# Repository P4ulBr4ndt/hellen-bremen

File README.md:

# Hellen-Bremen

**WIP. Untested.**

This is trying to be yet another HD ECU based on rusEFI.\
Commercial rusEFI based HD ECUs:\
https://www.nmstec.ca/product/hdrevb/ This seems to be the initial community development? 
https://impactwiringsolutions.com/ Commercial product

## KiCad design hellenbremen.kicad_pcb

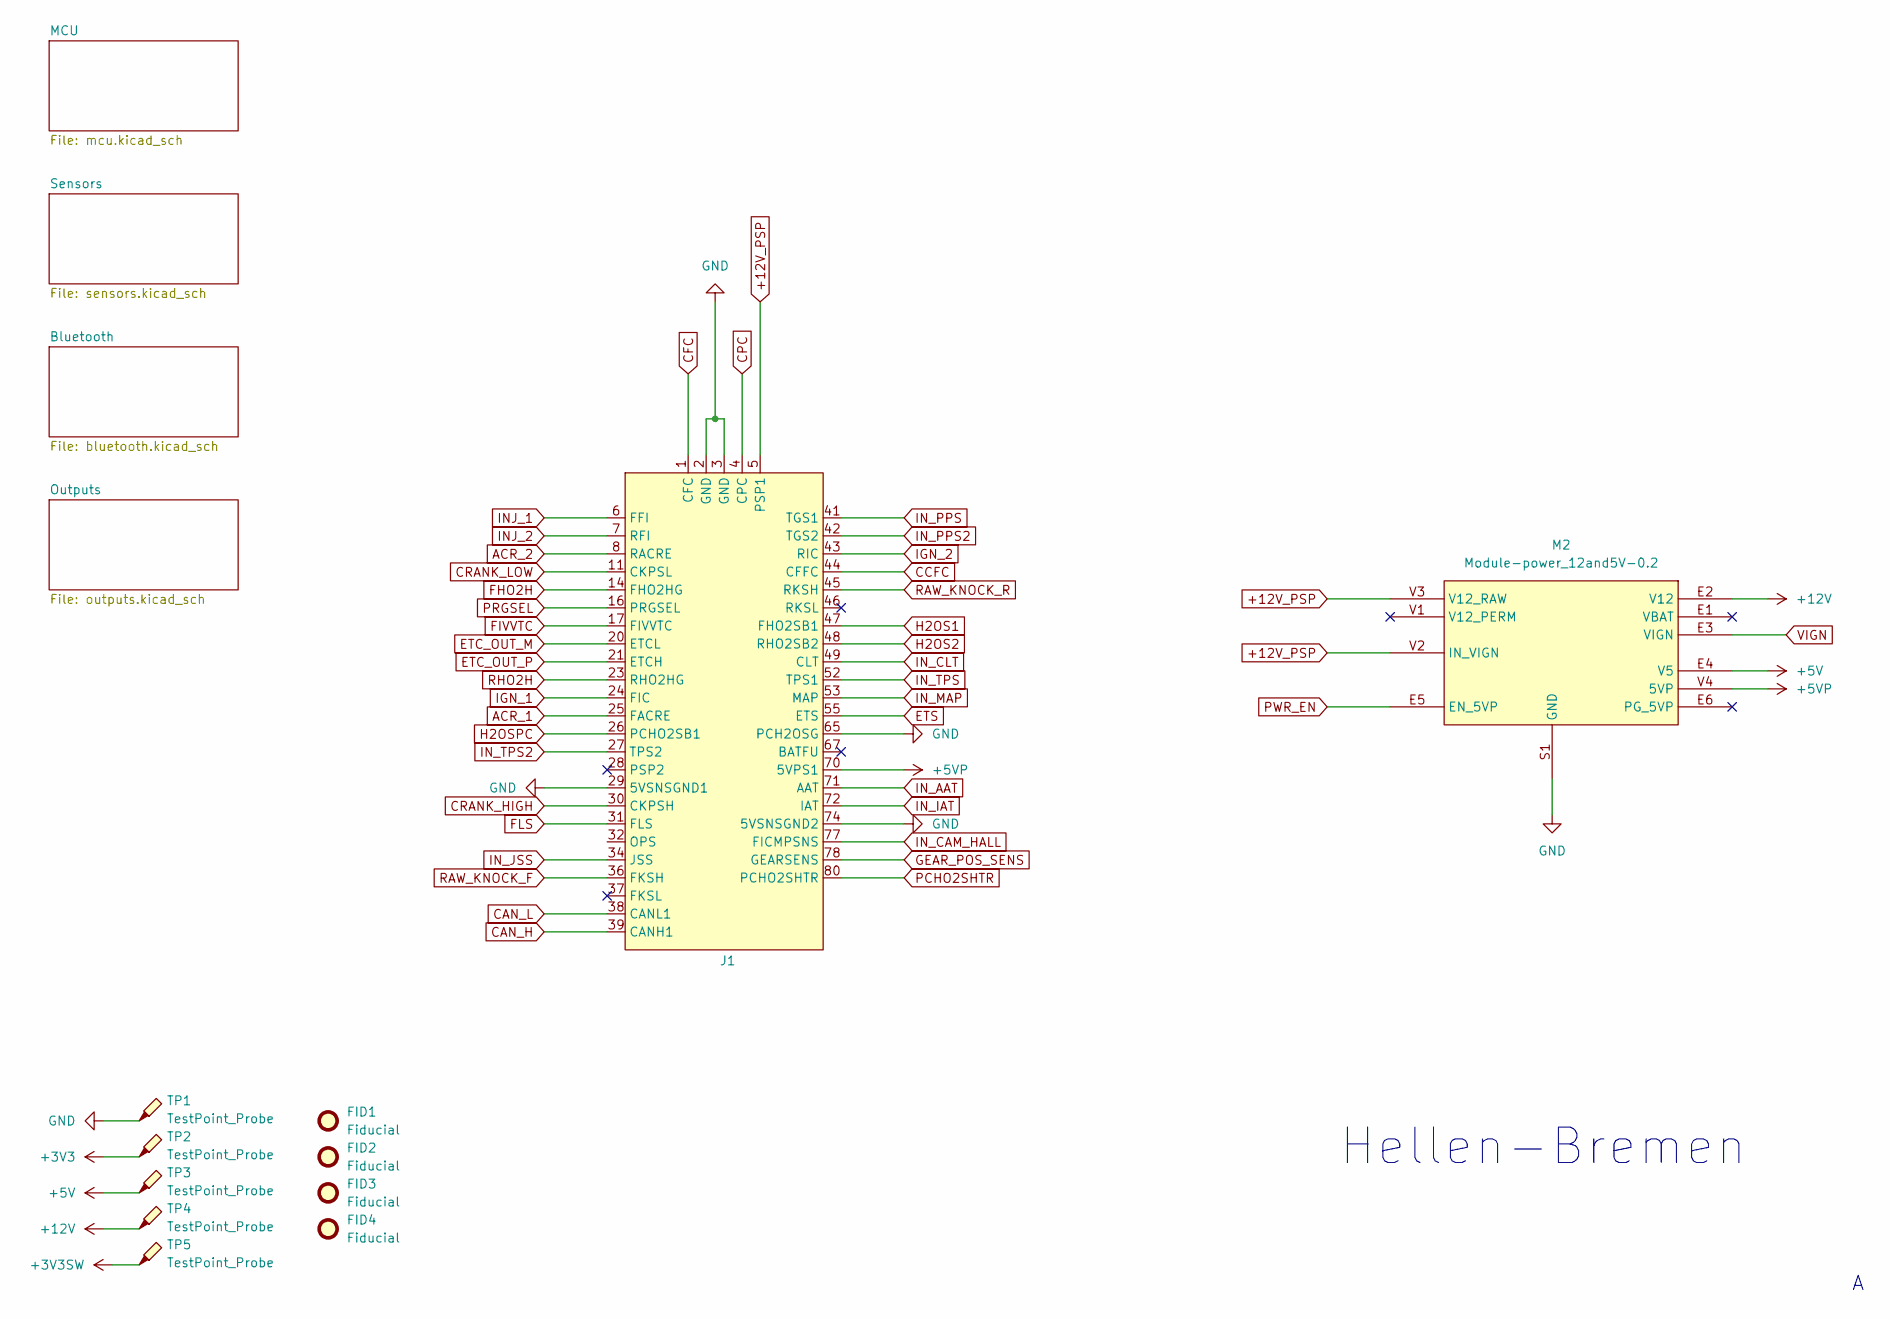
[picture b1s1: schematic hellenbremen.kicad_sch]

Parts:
FID1, FID2, FID3, FID4: Fiducial; Fiducial_1mm_Mask2mm
J1: HarleyDavidsonDelphi81
M2: Module-power_12and5V-0.2; power_12and5V
TP1, TP2, TP3, TP4, TP5: TestPoint_Probe; TestPoint_Pad_D2.0mm

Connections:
+3V3: TP2.1; also elsewhere on the board
+3V3SW: TP5.1; also elsewhere on the board
+5V: M2.E4 (V5), TP3.1; also elsewhere on the board
+5VP: J1.70 (5VPS1), M2.V4 (5VP)
+12V: M2.E2 (V12), TP4.1; also elsewhere on the board
+12V_PSP: J1.5 (PSP1), M2.V2 (IN_VIGN), M2.V3 (V12_RAW)
ACR_1: J1.25 (FACRE); also elsewhere on the board
ACR_2: J1.8 (RACRE); also elsewhere on the board
CAN_H: J1.39 (CANH1); also elsewhere on the board
CAN_L: J1.38 (CANL1); also elsewhere on the board
CCFC: J1.44 (CFFC); also elsewhere on the board
CFC: J1.1 (CFC); also elsewhere on the board
CPC: J1.4 (CPC); also elsewhere on the board
CRANK_HIGH: J1.30 (CKPSH); also elsewhere on the board
CRANK_LOW: J1.11 (CKPSL); also elsewhere on the board
ETC_OUT_M: J1.20 (ETCL); also elsewhere on the board
ETC_OUT_P: J1.21 (ETCH); also elsewhere on the board
ETS: J1.55 (ETS); also elsewhere on the board
FHO2H: J1.14 (FHO2HG); also elsewhere on the board
FIVVTC: J1.17 (FIVVTC); also elsewhere on the board
FLS: J1.31 (FLS); also elsewhere on the board
GEAR_POS_SENS: J1.78 (GEARSENS); also elsewhere on the board
GND: J1.2 (GND), J1.3 (GND), J1.29 (5VSNSGND1), J1.65 (PCH2OSG), J1.74 (5VSNSGND2), M2.S1 (GND), TP1.1; also elsewhere on the board
H2OS1: J1.47 (FHO2SB1); also elsewhere on the board
H2OS2: J1.48 (RHO2SB2); also elsewhere on the board
H2OSPC: J1.26 (PCHO2SB1); also elsewhere on the board
IGN_1: J1.24 (FIC); also elsewhere on the board
IGN_2: J1.43 (RIC); also elsewhere on the board
INJ_1: J1.6 (FFI); also elsewhere on the board
INJ_2: J1.7 (RFI); also elsewhere on the board
IN_AAT: J1.71 (AAT); also elsewhere on the board
IN_CAM_HALL: J1.77 (FICMPSNS); also elsewhere on the board
IN_CLT: J1.49 (CLT); also elsewhere on the board
IN_IAT: J1.72 (IAT); also elsewhere on the board
IN_JSS: J1.34 (JSS); also elsewhere on the board
IN_MAP: J1.53 (MAP); also elsewhere on the board
IN_PPS: J1.41 (TGS1); also elsewhere on the board
IN_PPS2: J1.42 (TGS2); also elsewhere on the board
IN_TPS: J1.52 (TPS1); also elsewhere on the board
IN_TPS2: J1.27 (TPS2); also elsewhere on the board
PCHO2SHTR: J1.80 (PCHO2SHTR); also elsewhere on the board
PRGSEL: J1.16 (PRGSEL); also elsewhere on the board
PWR_EN: M2.E5 (EN_5VP); also elsewhere on the board
RAW_KNOCK_F: J1.36 (FKSH); also elsewhere on the board
RAW_KNOCK_R: J1.45 (RKSH); also elsewhere on the board
RHO2H: J1.23 (RHO2HG); also elsewhere on the board
VIGN: M2.E3 (VIGN); also elsewhere on the board

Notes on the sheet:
Hellen-Bremen

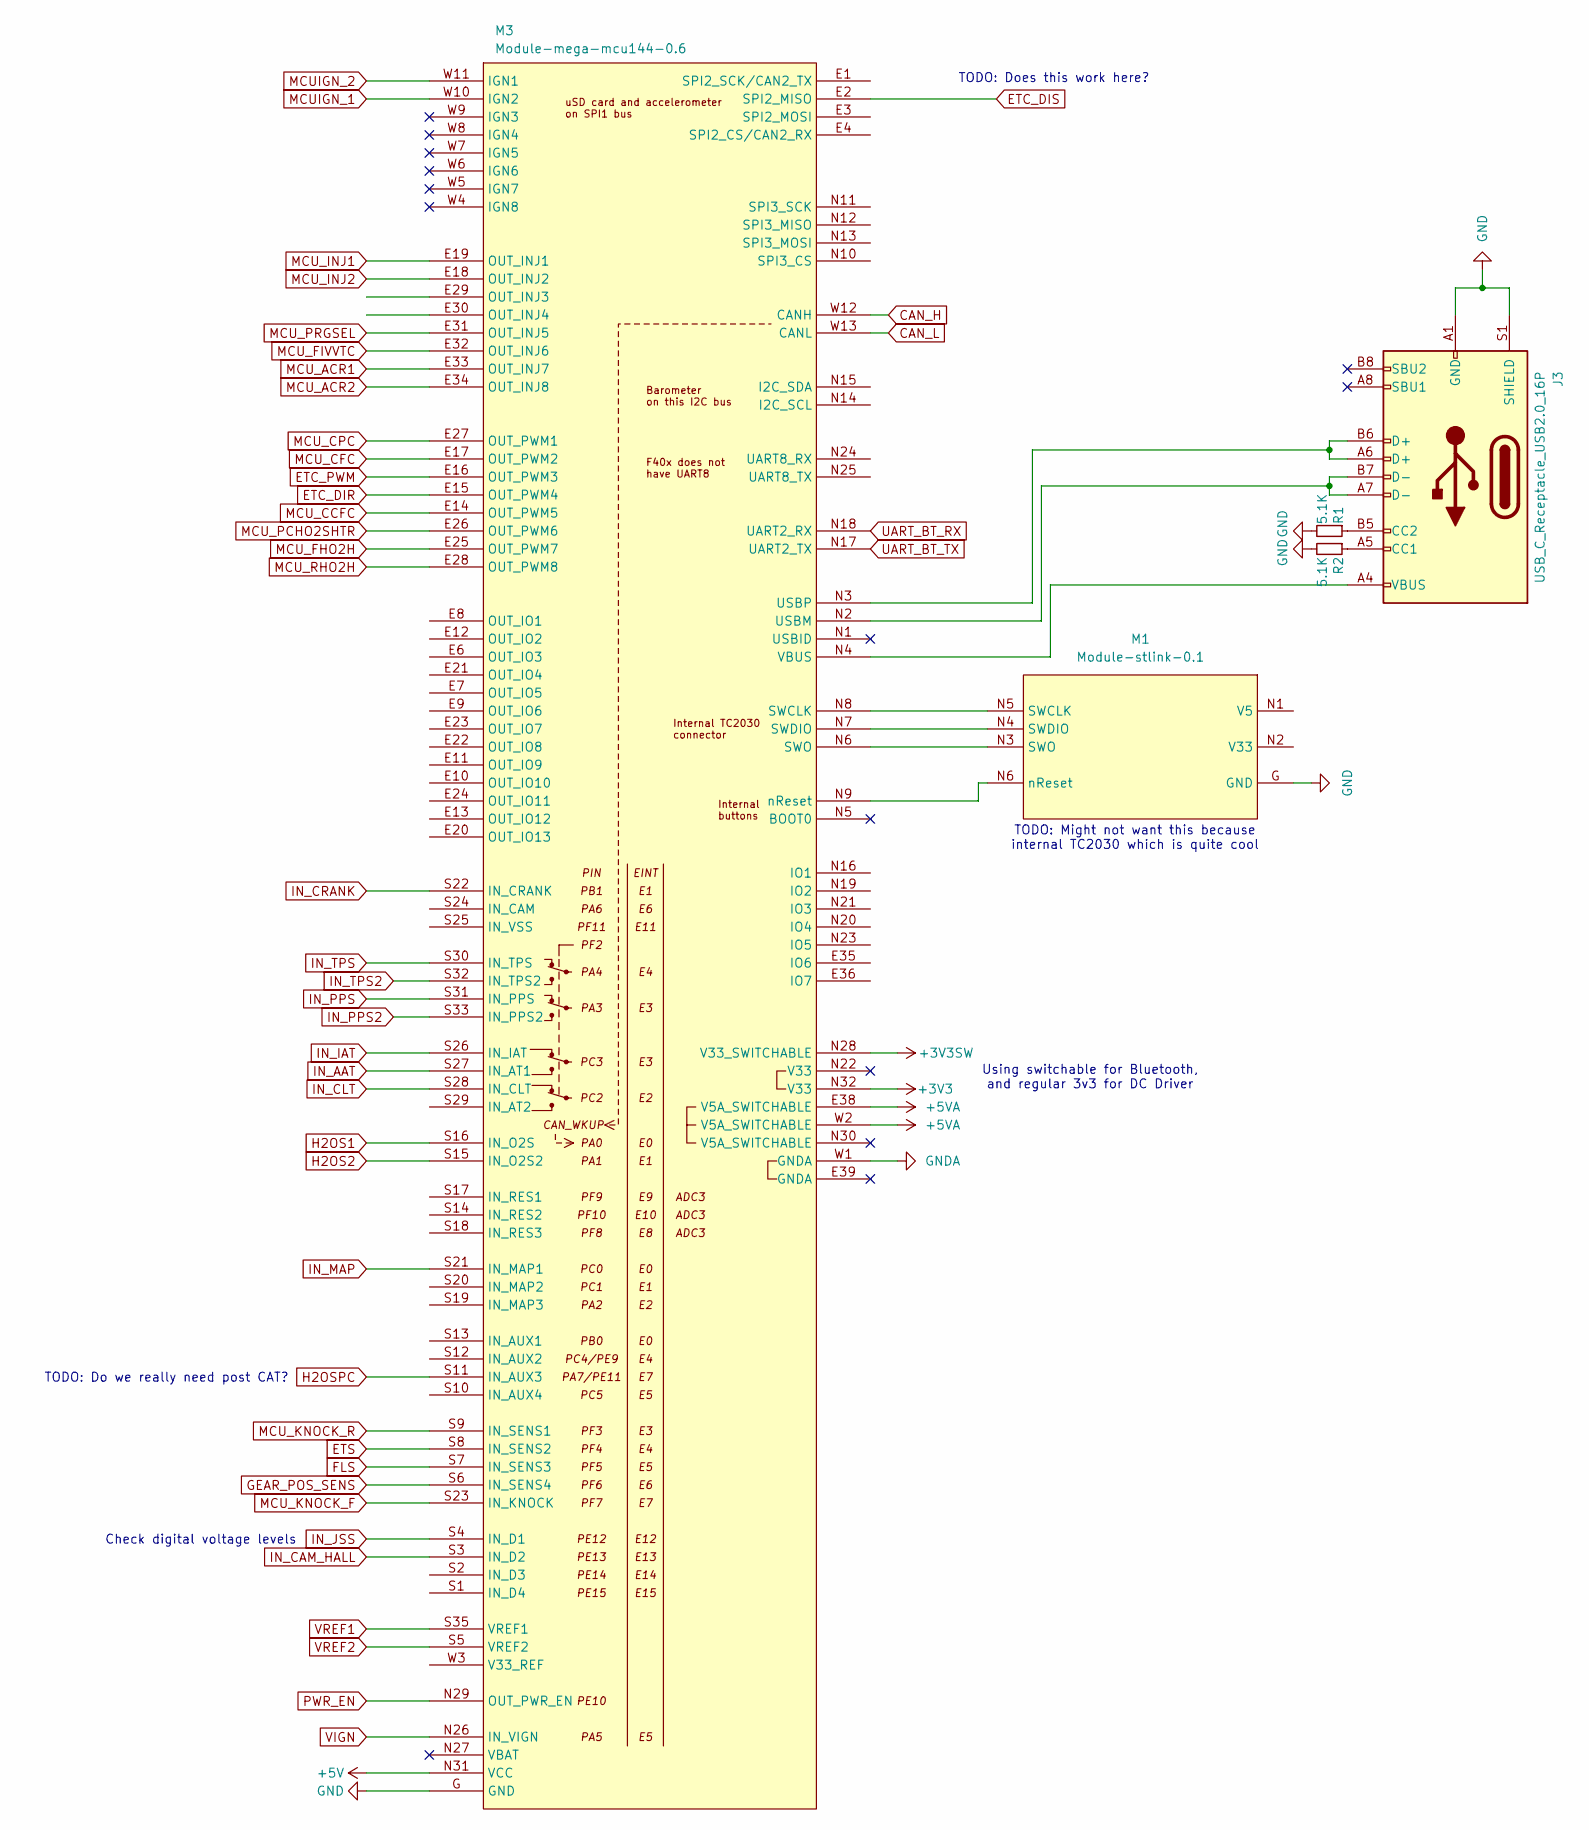
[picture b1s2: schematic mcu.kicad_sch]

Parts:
J3: USB_C_Receptacle_USB2.0_16P; USB_C_Receptacle_GCT_USB4110
M1: Module-stlink-0.1; stlink
M3: Module-mega-mcu144-0.6; mega-mcu144
R1, R2: 5.1K; R_0402_1005Metric

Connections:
+3V3: M3.N32 (V33); also elsewhere on the board
+3V3SW: M3.N28 (V33_SWITCHABLE); also elsewhere on the board
+5V: M3.N31 (VCC); also elsewhere on the board
+5VA: M3.E38 (V5A_SWITCHABLE), M3.W2 (V5A_SWITCHABLE); also elsewhere on the board
CAN_H: M3.W12 (CANH); also elsewhere on the board
CAN_L: M3.W13 (CANL); also elsewhere on the board
ETC_DIR: M3.E15 (OUT_PWM4); also elsewhere on the board
ETC_DIS: M3.E2 (SPI2_MISO); also elsewhere on the board
ETC_PWM: M3.E16 (OUT_PWM3); also elsewhere on the board
ETS: M3.S8 (IN_SENS2); also elsewhere on the board
FLS: M3.S7 (IN_SENS3); also elsewhere on the board
GEAR_POS_SENS: M3.S6 (IN_SENS4); also elsewhere on the board
GND: J3.A1 (GND), J3.A12 (GND), J3.B1 (GND), J3.B12 (GND), J3.S1 (SHIELD), M1.G (GND), M3.G (GND), R1.2, R2.2; also elsewhere on the board
GNDA: M3.W1 (GNDA)
H2OS1: M3.S16 (IN_O2S); also elsewhere on the board
H2OS2: M3.S15 (IN_O2S2); also elsewhere on the board
H2OSPC: M3.S11 (IN_AUX3); also elsewhere on the board
IN_AAT: M3.S27 (IN_AT1); also elsewhere on the board
IN_CAM_HALL: M3.S3 (IN_D2); also elsewhere on the board
IN_CLT: M3.S28 (IN_CLT); also elsewhere on the board
IN_CRANK: M3.S22 (IN_CRANK); also elsewhere on the board
IN_IAT: M3.S26 (IN_IAT); also elsewhere on the board
IN_JSS: M3.S4 (IN_D1); also elsewhere on the board
IN_MAP: M3.S21 (IN_MAP1); also elsewhere on the board
IN_PPS: M3.S31 (IN_PPS); also elsewhere on the board
IN_PPS2: M3.S33 (IN_PPS2); also elsewhere on the board
IN_TPS: M3.S30 (IN_TPS); also elsewhere on the board
IN_TPS2: M3.S32 (IN_TPS2); also elsewhere on the board
MCUIGN_1: M3.W10 (IGN2); also elsewhere on the board
MCUIGN_2: M3.W11 (IGN1); also elsewhere on the board
MCU_ACR1: M3.E33 (OUT_INJ7); also elsewhere on the board
MCU_ACR2: M3.E34 (OUT_INJ8); also elsewhere on the board
MCU_CCFC: M3.E14 (OUT_PWM5); also elsewhere on the board
MCU_CFC: M3.E17 (OUT_PWM2); also elsewhere on the board
MCU_CPC: M3.E27 (OUT_PWM1); also elsewhere on the board
MCU_FHO2H: M3.E25 (OUT_PWM7); also elsewhere on the board
MCU_FIVVTC: M3.E32 (OUT_INJ6); also elsewhere on the board
MCU_INJ1: M3.E19 (OUT_INJ1); also elsewhere on the board
MCU_INJ2: M3.E18 (OUT_INJ2); also elsewhere on the board
MCU_KNOCK_F: M3.S23 (IN_KNOCK); also elsewhere on the board
MCU_KNOCK_R: M3.S9 (IN_SENS1); also elsewhere on the board
MCU_PCHO2SHTR: M3.E26 (OUT_PWM6); also elsewhere on the board
MCU_PRGSEL: M3.E31 (OUT_INJ5); also elsewhere on the board
MCU_RHO2H: M3.E28 (OUT_PWM8); also elsewhere on the board
unnamed: J3.A5 (CC1), R2.1
unnamed: J3.B5 (CC2), R1.1
unnamed: M1.N5 (SWCLK), M3.N8 (SWCLK)
unnamed: M1.N4 (SWDIO), M3.N7 (SWDIO)
unnamed: M1.N3 (SWO), M3.N6 (SWO)
unnamed: M1.N6 (nReset), M3.N9 (nReset)
unnamed: J3.A7 (D-), J3.B7 (D-), M3.N2 (USBM)
unnamed: J3.A6 (D+), J3.B6 (D+), M3.N3 (USBP)
unnamed: J3.A4 (VBUS), J3.A9 (VBUS), J3.B4 (VBUS), J3.B9 (VBUS), M3.N4 (VBUS)
PWR_EN: M3.N29 (OUT_PWR_EN); also elsewhere on the board
UART_BT_RX: M3.N18 (UART2_RX); also elsewhere on the board
UART_BT_TX: M3.N17 (UART2_TX); also elsewhere on the board
VIGN: M3.N26 (IN_VIGN); also elsewhere on the board
VREF1: M3.S35 (VREF1); also elsewhere on the board
VREF2: M3.S5 (VREF2); also elsewhere on the board

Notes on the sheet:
Using switchable for Bluetooth, and regular 3v3 for DC Driver
TODO: Might not want this because internal TC2030 which is quite cool
TODO: Does this work here?
TODO: Do we really need post CAT?
Check digital voltage levels

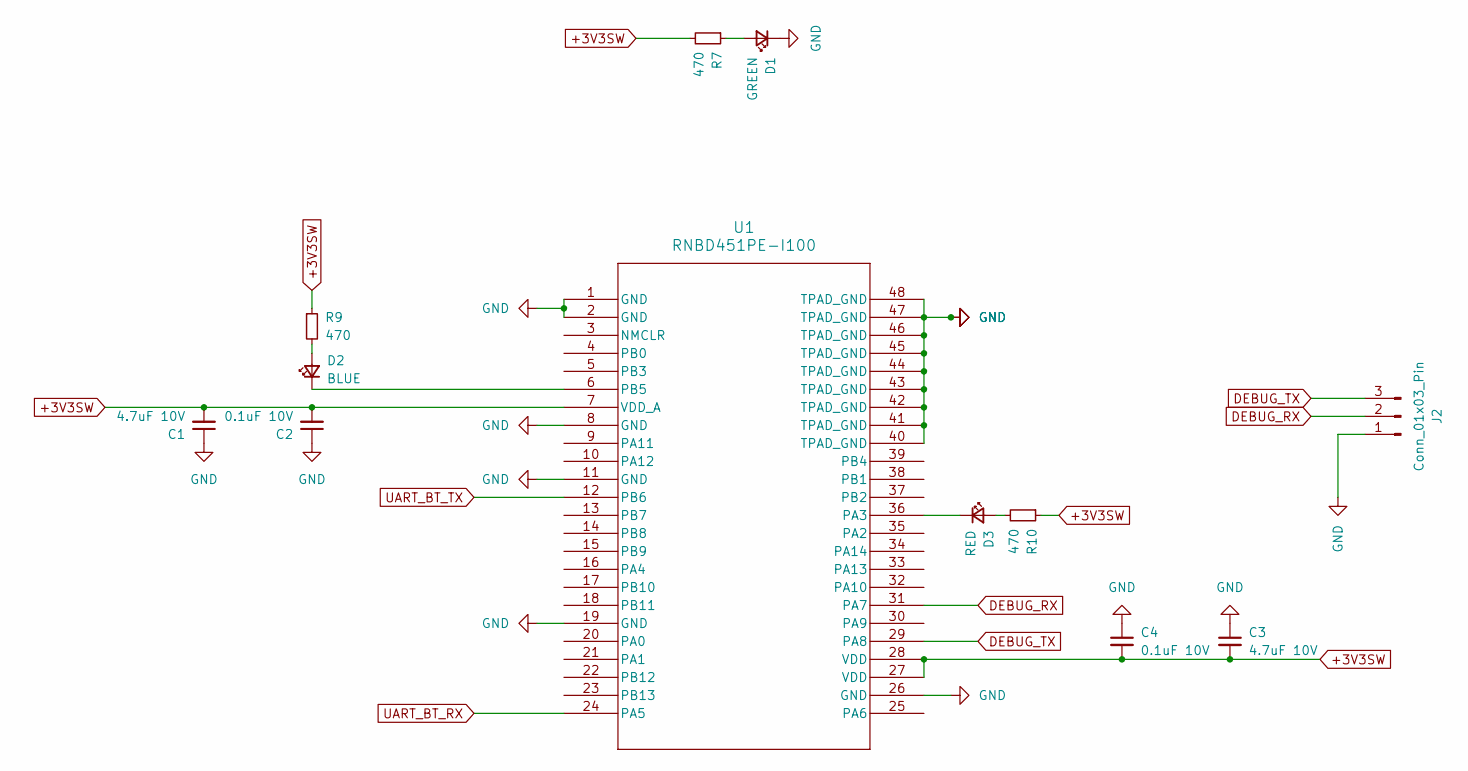
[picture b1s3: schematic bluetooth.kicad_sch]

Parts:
C1, C3: 4.7uF 10V; C_0603_1608Metric
C2, C4: 0.1uF 10V; C_0402_1005Metric
D1: GREEN; LED_0402_1005Metric
D2: BLUE; LED_0402_1005Metric
D3: RED; LED_0402_1005Metric
J2: Conn_01x03_Pin; PinHeader_1x03_P2.54mm_Vertical
R7, R9, R10: 470; R_0402_1005Metric
U1: RNBD451PE-I100; MOD39_15p5X20p7X2p8_ZSX_MCH

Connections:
+3V3SW: C1.2, C2.2, C3.2, C4.2, R7.2, R9.1, R10.1, U1.7 (VDD_A), U1.27 (VDD), U1.28 (VDD); also elsewhere on the board
DEBUG_RX: J2.2, U1.31 (PA7)
DEBUG_TX: J2.3, U1.29 (PA8)
GND: C1.1, C2.1, C3.1, C4.1, D1.1 (K), J2.1, U1.1 (GND), U1.2 (GND), U1.8 (GND), U1.11 (GND), U1.19 (GND), U1.26 (GND), U1.40 (TPAD_GND), U1.41 (TPAD_GND), U1.42 (TPAD_GND), U1.43 (TPAD_GND), U1.44 (TPAD_GND), U1.45 (TPAD_GND), U1.46 (TPAD_GND), U1.47 (TPAD_GND), U1.48 (TPAD_GND); also elsewhere on the board
unnamed: D1.2 (A), R7.1
unnamed: D2.2 (A), R9.2
unnamed: D2.1 (K), U1.6 (PB5)
unnamed: D3.2 (A), R10.2
unnamed: D3.1 (K), U1.36 (PA3)
UART_BT_RX: U1.24 (PA5); also elsewhere on the board
UART_BT_TX: U1.12 (PB6); also elsewhere on the board

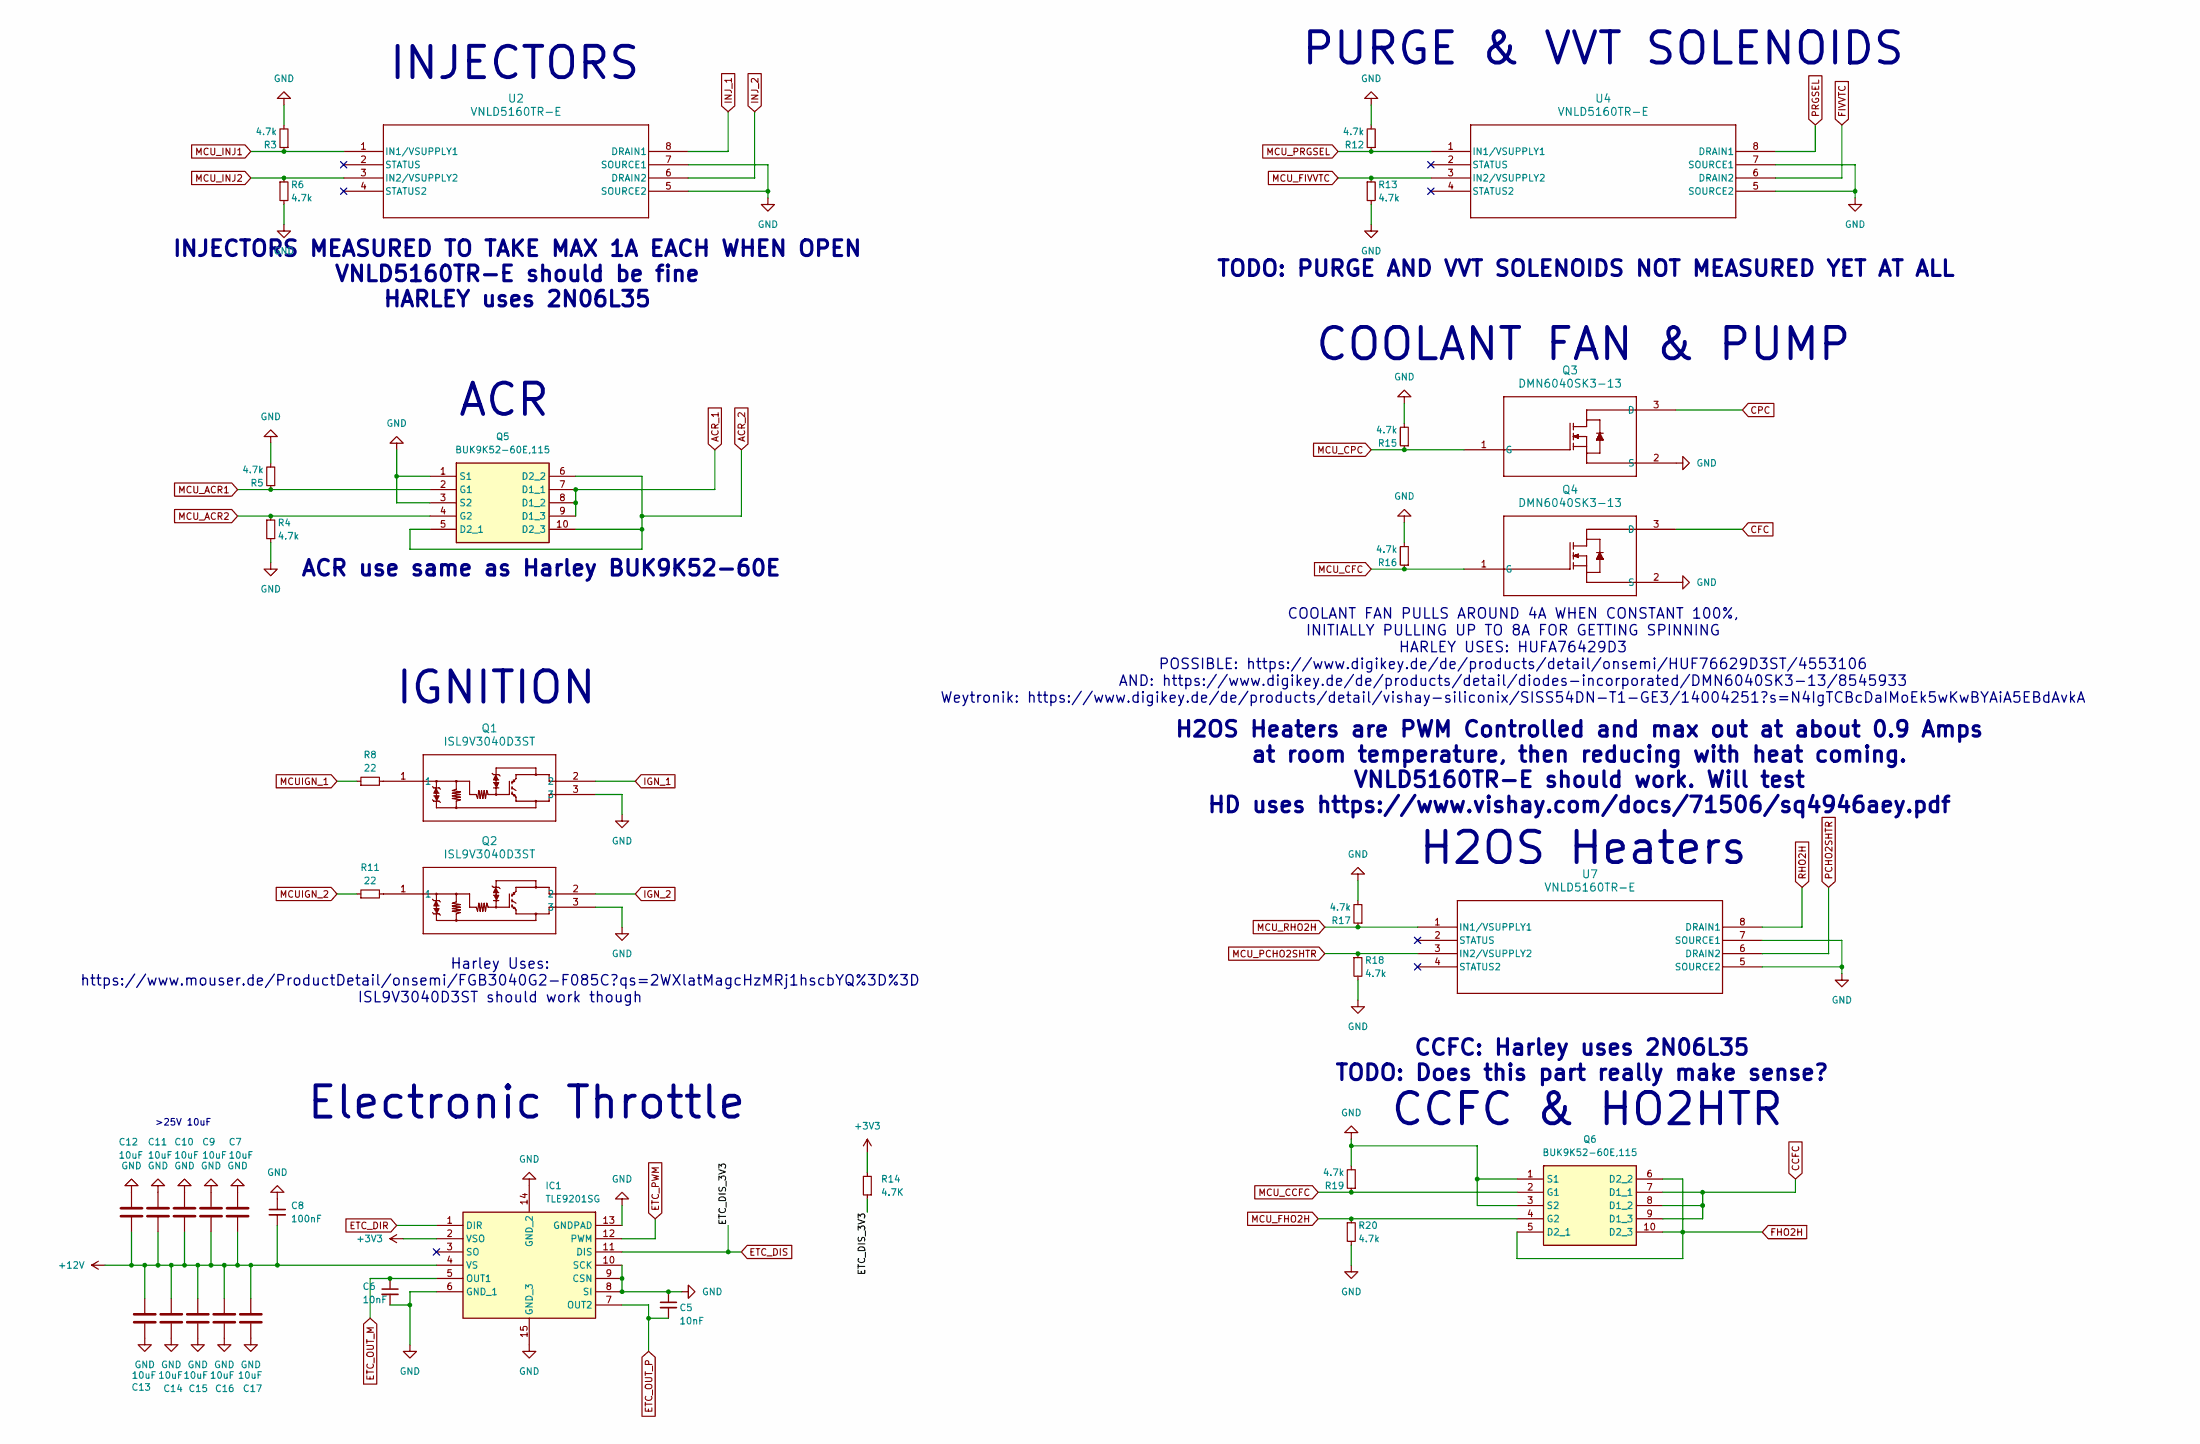
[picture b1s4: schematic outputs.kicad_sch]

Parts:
C5, C6: 10nF; C_0402_1005Metric
C7, C9, C10, C11, C12, C13, C14, C15, C16, C17: 10uF; C_0805_2012Metric
C8: 100nF; C_0603_1608Metric
IC1: TLE9201SG; Mouser Part Number 726-TLE9201SG
Q1, Q2: ISL9V3040D3ST; TO-252AA_ONS
Q3, Q4: DMN6040SK3-13; D-PAK_DMN6040SK3-13_DIO
Q5, Q6: BUK9K52-60E,115; BUK7K6R840E115; Mouser Part Number 771-BUK9K52-60E115
R3, R4, R5, R6, R12, R13, R15, R16, R17, R18, R19, R20: 4.7k; R_0402_1005Metric
R8, R11: 22; R_0603_1608Metric
R14: 4.7K; R_0402_1005Metric
U2, U4, U7: VNLD5160TR-E; SO_160TR-E_STM

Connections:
+3V3: IC1.2 (VSO), R14.2; also elsewhere on the board
+12V: C7.2, C8.2, C9.2, C10.2, C11.2, C12.2, C13.2, C14.2, C15.2, C16.2, C17.2, IC1.4 (VS); also elsewhere on the board
ACR_1: Q5.7 (D1_1), Q5.8 (D1_2), Q5.9 (D1_3); also elsewhere on the board
ACR_2: Q5.5 (D2_1), Q5.6 (D2_2), Q5.10 (D2_3); also elsewhere on the board
CCFC: Q6.7 (D1_1), Q6.8 (D1_2), Q6.9 (D1_3); also elsewhere on the board
CFC: Q4.3 (D); also elsewhere on the board
CPC: Q3.3 (D); also elsewhere on the board
ETC_DIR: IC1.1 (DIR); also elsewhere on the board
ETC_DIS: IC1.11 (DIS), R14.1; also elsewhere on the board
ETC_OUT_M: C6.1, IC1.5 (OUT1); also elsewhere on the board
ETC_OUT_P: C5.2, IC1.7 (OUT2); also elsewhere on the board
ETC_PWM: IC1.12 (PWM); also elsewhere on the board
FHO2H: Q6.5 (D2_1), Q6.6 (D2_2), Q6.10 (D2_3); also elsewhere on the board
FIVVTC: U4.6 (DRAIN2); also elsewhere on the board
GND: C5.1, C6.2, C7.1, C8.1, C9.1, C10.1, C11.1, C12.1, C13.1, C14.1, C15.1, C16.1, C17.1, IC1.6 (GND_1), IC1.8 (SI), IC1.9 (CSN), IC1.10 (SCK), IC1.13 (GNDPAD), IC1.14 (GND_2), IC1.15 (GND_3), Q1.3, Q2.3, Q3.2 (S), Q4.2 (S), Q5.1 (S1), Q5.3 (S2), Q6.1 (S1), Q6.3 (S2), R3.2, R4.2, R5.2, R6.2, R12.2, R13.2, R15.2, R16.2, R17.2, R18.2, R19.2, R20.2, U2.5 (SOURCE2), U2.7 (SOURCE1), U4.5 (SOURCE2), U4.7 (SOURCE1), U7.5 (SOURCE2), U7.7 (SOURCE1); also elsewhere on the board
IGN_1: Q1.2; also elsewhere on the board
IGN_2: Q2.2; also elsewhere on the board
INJ_1: U2.8 (DRAIN1); also elsewhere on the board
INJ_2: U2.6 (DRAIN2); also elsewhere on the board
MCUIGN_1: R8.1; also elsewhere on the board
MCUIGN_2: R11.1; also elsewhere on the board
MCU_ACR1: Q5.2 (G1), R5.1; also elsewhere on the board
MCU_ACR2: Q5.4 (G2), R4.1; also elsewhere on the board
MCU_CCFC: Q6.2 (G1), R19.1; also elsewhere on the board
MCU_CFC: Q4.1 (G), R16.1; also elsewhere on the board
MCU_CPC: Q3.1 (G), R15.1; also elsewhere on the board
MCU_FHO2H: Q6.4 (G2), R20.1; also elsewhere on the board
MCU_FIVVTC: R13.1, U4.3 (IN2/VSUPPLY2); also elsewhere on the board
MCU_INJ1: R3.1, U2.1 (IN1/VSUPPLY1); also elsewhere on the board
MCU_INJ2: R6.1, U2.3 (IN2/VSUPPLY2); also elsewhere on the board
MCU_PCHO2SHTR: R18.1, U7.3 (IN2/VSUPPLY2); also elsewhere on the board
MCU_PRGSEL: R12.1, U4.1 (IN1/VSUPPLY1); also elsewhere on the board
MCU_RHO2H: R17.1, U7.1 (IN1/VSUPPLY1); also elsewhere on the board
unnamed: Q1.1, R8.2
unnamed: Q2.1, R11.2
PCHO2SHTR: U7.6 (DRAIN2); also elsewhere on the board
PRGSEL: U4.8 (DRAIN1); also elsewhere on the board
RHO2H: U7.8 (DRAIN1); also elsewhere on the board

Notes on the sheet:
COOLANT FAN PULLS AROUND 4A WHEN CONSTANT 100%, INITIALLY PULLING UP TO 8A FOR GETTING SPINNING HARLEY USES: HUFA76429D3 POSSIBLE: https://www.digikey.de/de/products/detail/onsemi/HUF76629D3ST/4553106 AND: https://www.digikey.de/de/products/detail/diodes-incorporated/DMN6040SK3-13/8545933 Weytronik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
PURGE & VVT SOLENOIDS
INJECTORS MEASURED TO TAKE MAX 1A EACH WHEN OPEN VNLD5160TR-E should be fine HARLEY uses 2N06L35
INJECTORS
H2OS Heaters are PWM Controlled and max out at about 0.9 Amps at room temperature, then reducing with heat coming. VNLD5160TR-E should work. Will test HD uses https://www.vishay.com/docs/71506/sq4946aey.pdf
TODO: PURGE AND VVT SOLENOIDS NOT MEASURED YET AT ALL
ACR
Harley Uses: https://www.mouser.de/ProductDetail/onsemi/FGB3040G2-F085C?qs=2WXlatMagcHzMRj1hscbYQ%3D%3D ISL9V3040D3ST should work though
>25V 10uF
COOLANT FAN & PUMP
IGNITION
ACR use same as Harley BUK9K52-60E
Electronic Throttle
CCFC & HO2HTR
H2OS Heaters
CCFC: Harley uses 2N06L35 TODO: Does this part really make sense?

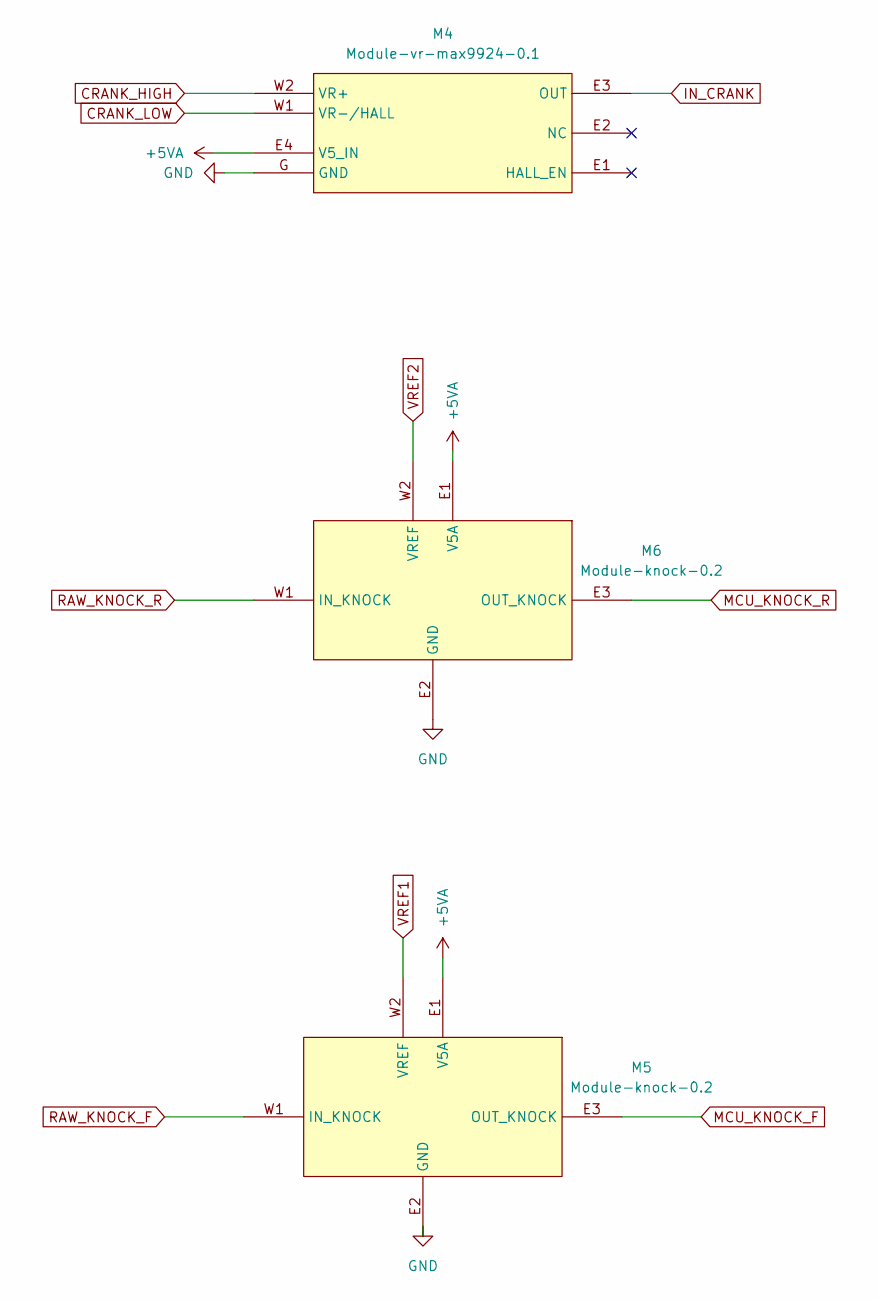
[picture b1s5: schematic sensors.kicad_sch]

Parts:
M4: Module-vr-max9924-0.1; vr-max9924
M5, M6: Module-knock-0.2; knock

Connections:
+5VA: M4.E4 (V5_IN), M5.E1 (V5A), M6.E1 (V5A); also elsewhere on the board
CRANK_HIGH: M4.W2 (VR+); also elsewhere on the board
CRANK_LOW: M4.W1 (VR-/HALL); also elsewhere on the board
GND: M4.G (GND), M5.E2 (GND), M6.E2 (GND); also elsewhere on the board
IN_CRANK: M4.E3 (OUT); also elsewhere on the board
MCU_KNOCK_F: M5.E3 (OUT_KNOCK); also elsewhere on the board
MCU_KNOCK_R: M6.E3 (OUT_KNOCK); also elsewhere on the board
RAW_KNOCK_F: M5.W1 (IN_KNOCK); also elsewhere on the board
RAW_KNOCK_R: M6.W1 (IN_KNOCK); also elsewhere on the board
VREF1: M5.W2 (VREF); also elsewhere on the board
VREF2: M6.W2 (VREF); also elsewhere on the board

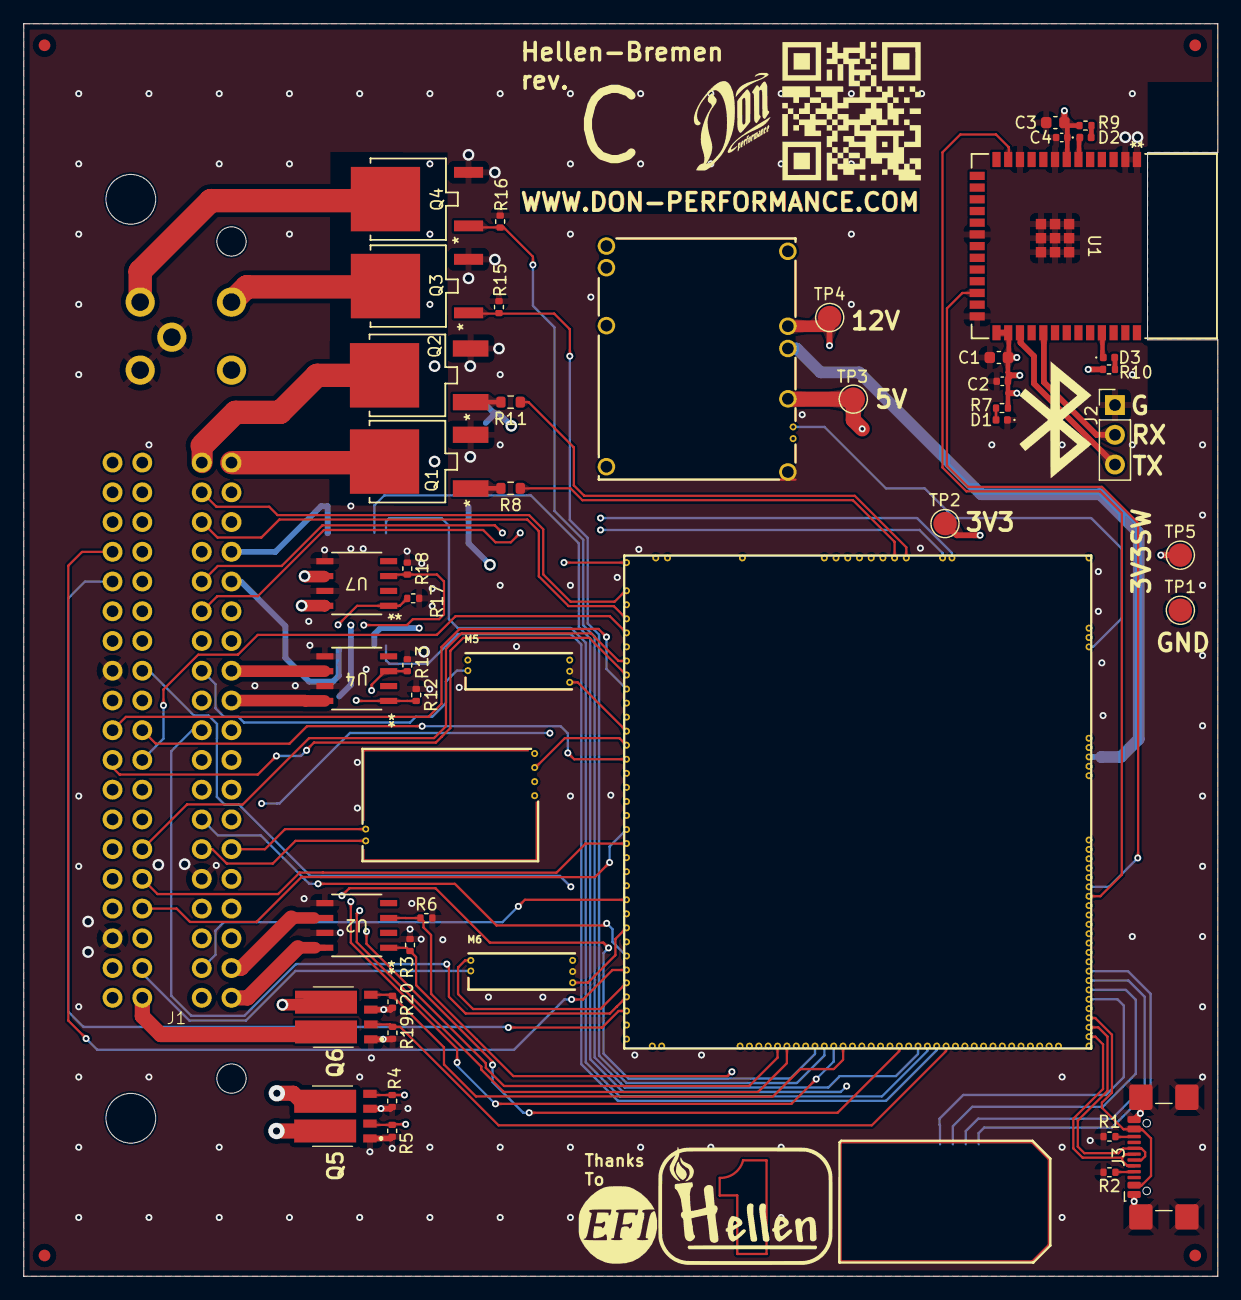
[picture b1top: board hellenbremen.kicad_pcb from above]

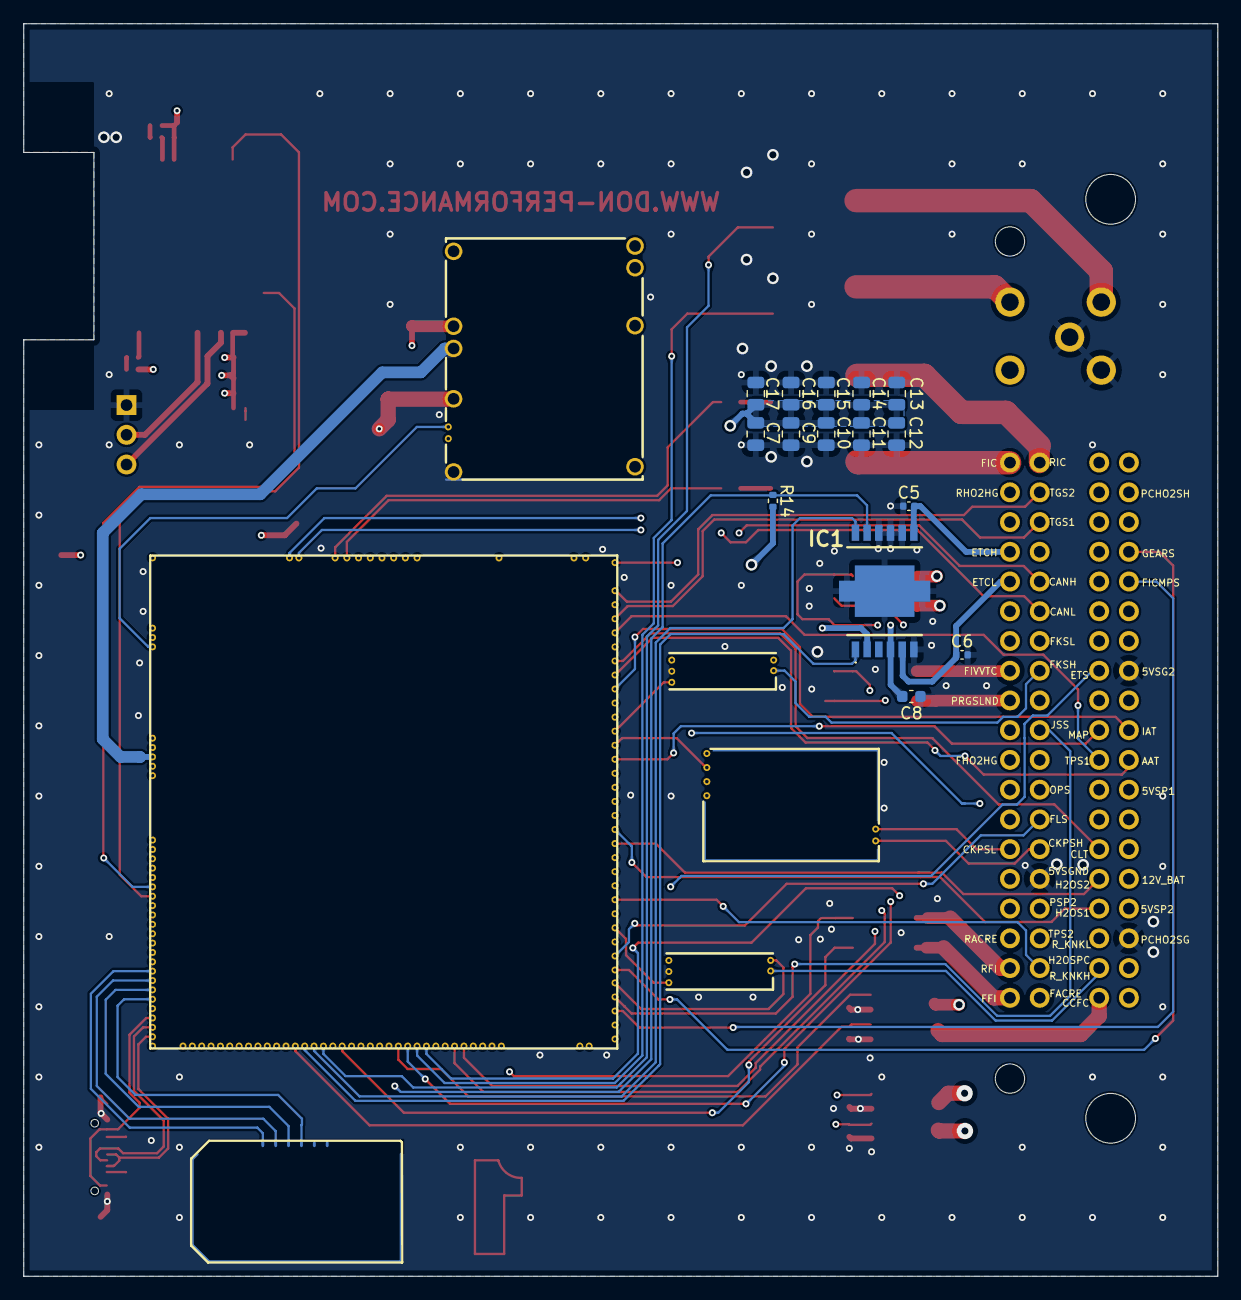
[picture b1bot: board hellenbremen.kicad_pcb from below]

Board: 4 copper layers, 102.0 x 107.0 mm, 69 parts (15 on the bottom side), 90 nets.

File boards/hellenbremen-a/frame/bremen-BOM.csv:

Comment,Designator,Footprint,LCSC Part #
"4.7uF 10V","C1","C0603",""
"0.1uF 10V","C2","C0402",""
"4.7uF 10V","C3","C0603",""
"0.1uF 10V","C4","C0402",""
"10nF","C5","C0402",""
"10nF","C6","C0402",""
"10uF","C7","C0805",""
"100nF","C8","C0603",""
"10uF","C9","C0805",""
"10uF","C10","C0805",""
"10uF","C11","C0805",""
"10uF","C12","C0805",""
"10uF","C13","C0805",""
"10uF","C14","C0805",""
"10uF","C15","C0805",""
"10uF","C16","C0805",""
"10uF","C17","C0805",""
"GREEN","D1","LED_0402_1005Metric",""
"BLUE","D2","LED_0402_1005Metric",""
"RED","D3","LED_0402_1005Metric",""
"TLE9201SG","IC1","TLE9201SG",""
"Conn_01x03_Pin","J2","PinHeader_1x03_P2.54mm_Vertical",""
"USB_C_Receptacle_USB2.0_16P","J3","USB_C_Receptacle_GCT_USB4110",""
"Module:stlink/0.1","M1","stlink",""
"Module:power_12and5V/0.2","M2","power_12and5V",""
"Module:mega-mcu144/0.6","M3","mega-mcu144",""
"Module:vr-max9924/0.1","M4","vr-max9924",""
"Module:knock/0.2","M5","knock",""
"Module:knock/0.2","M6","knock",""
"ISL9V3040D3ST","Q1","TO-252AA_ONS",""
"ISL9V3040D3ST","Q2","TO-252AA_ONS",""
"DMN6040SK3-13","Q3","D-PAK_DMN6040SK3-13_DIO",""
"DMN6040SK3-13","Q4","D-PAK_DMN6040SK3-13_DIO",""
"BUK9K52-60E,115","Q5","BUK7K6R840E115",""
"5.1K","R1","R0402",""
"5.1K","R2","R0402",""
"4.7k","R3","R0402",""
"4.7k","R4","R0402",""
"4.7k","R5","R0402",""
"4.7k","R6","R0402",""
"470","R7","R0402",""
"22","R8","R0603",""
"470","R9","R0402",""
"470","R10","R0402",""
"22","R11","R0603",""
"4.7k","R12","R0402",""
"4.7k","R13","R0402",""
"4.7K","R14","R0402",""
"4.7k","R15","R0402",""
"4.7k","R16","R0402",""
"4.7k","R17","R0402",""
"4.7k","R18","R0402",""
"4.7k","R19","R0402",""
"4.7k","R20","R0402",""
"RNBD451PE-I100","U1","MOD39_15p5X20p7X2p8_ZSX_MCH",""
"VNLD5160TR-E","U2","SO_160TR-E_STM",""
"VNLD5160TR-E","U4","SO_160TR-E_STM",""
"VNLD5160TR-E","U7","SO_160TR-E_STM",""
"VNLD5160TR-E","U8","SO_160TR-E_STM",""
